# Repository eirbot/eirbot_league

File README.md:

# eirbot_league
Rocket League inspired robots

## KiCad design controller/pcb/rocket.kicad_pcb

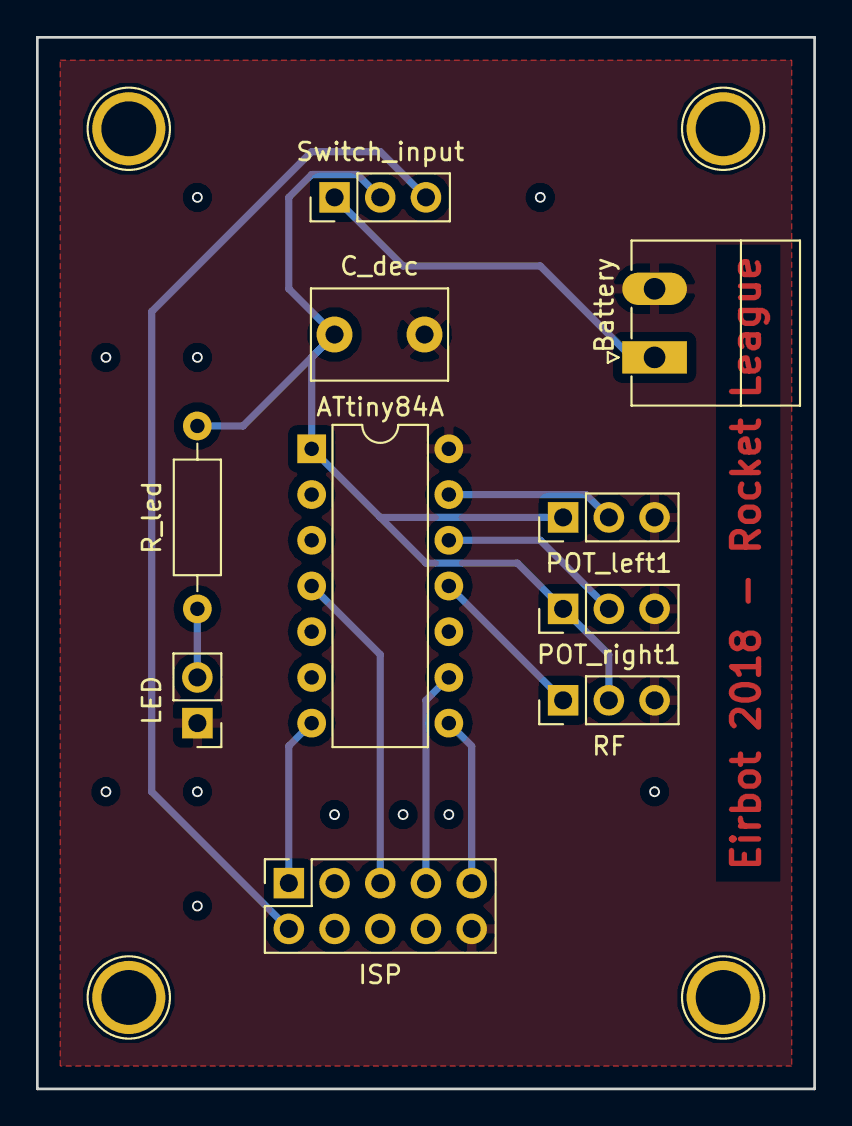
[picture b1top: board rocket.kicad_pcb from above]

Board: 2 copper layers, 43.2 x 58.4 mm, 10 parts (0 on the bottom side), 12 nets.

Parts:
ATtiny84A: ATtiny84A-PU; DIP-14_W7.62mm
Battery: Conn_01x02_Male; PhoenixContact_MC-G_02x3.81mm_Angled
C_dec: 10 nF; C_Disc_D7.5mm_W5.0mm_P5.00mm
ISP: Conn_02x05_Odd_Even; Pin_Header_Straight_2x05_Pitch2.54mm
LED: Conn_01x02_Female; Pin_Header_Straight_1x02_Pitch2.54mm
POT_left1: 10 kR; Pin_Header_Straight_1x03_Pitch2.54mm
POT_right1: 10 kR; Pin_Header_Straight_1x03_Pitch2.54mm
RF: Conn_01x03_Female; Pin_Header_Straight_1x03_Pitch2.54mm
R_led: R_led; R_Axial_DIN0207_L6.3mm_D2.5mm_P10.16mm_Horizontal
Switch_input: Conn_01x03_Female; Pin_Header_Straight_1x03_Pitch2.54mm

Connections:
GND: ATtiny84A.14, Battery.2, C_dec.2, ISP.10, LED.1, POT_left1.3, POT_right1.3, RF.3
unnamed: ATtiny84A.1, C_dec.1, POT_left1.1, POT_right1.1, RF.2, R_led.1, Switch_input.2
unnamed: LED.2, R_led.2
unnamed: Battery.1, Switch_input.1
unnamed: ATtiny84A.7, ISP.1
unnamed: ISP.2, Switch_input.3
unnamed: ATtiny84A.4, ISP.5
unnamed: ATtiny84A.9, ISP.7
unnamed: ATtiny84A.8, ISP.9
unnamed: ATtiny84A.12, POT_right1.2
unnamed: ATtiny84A.13, POT_left1.2
unnamed: ATtiny84A.11, RF.1

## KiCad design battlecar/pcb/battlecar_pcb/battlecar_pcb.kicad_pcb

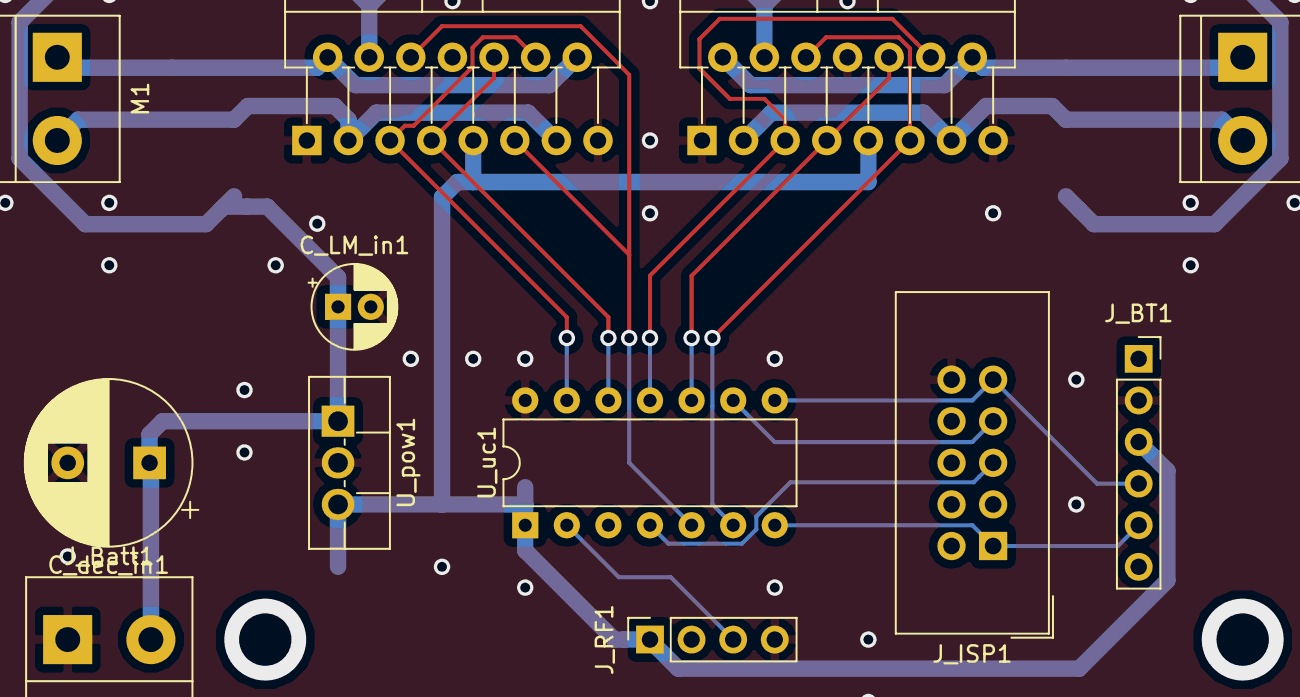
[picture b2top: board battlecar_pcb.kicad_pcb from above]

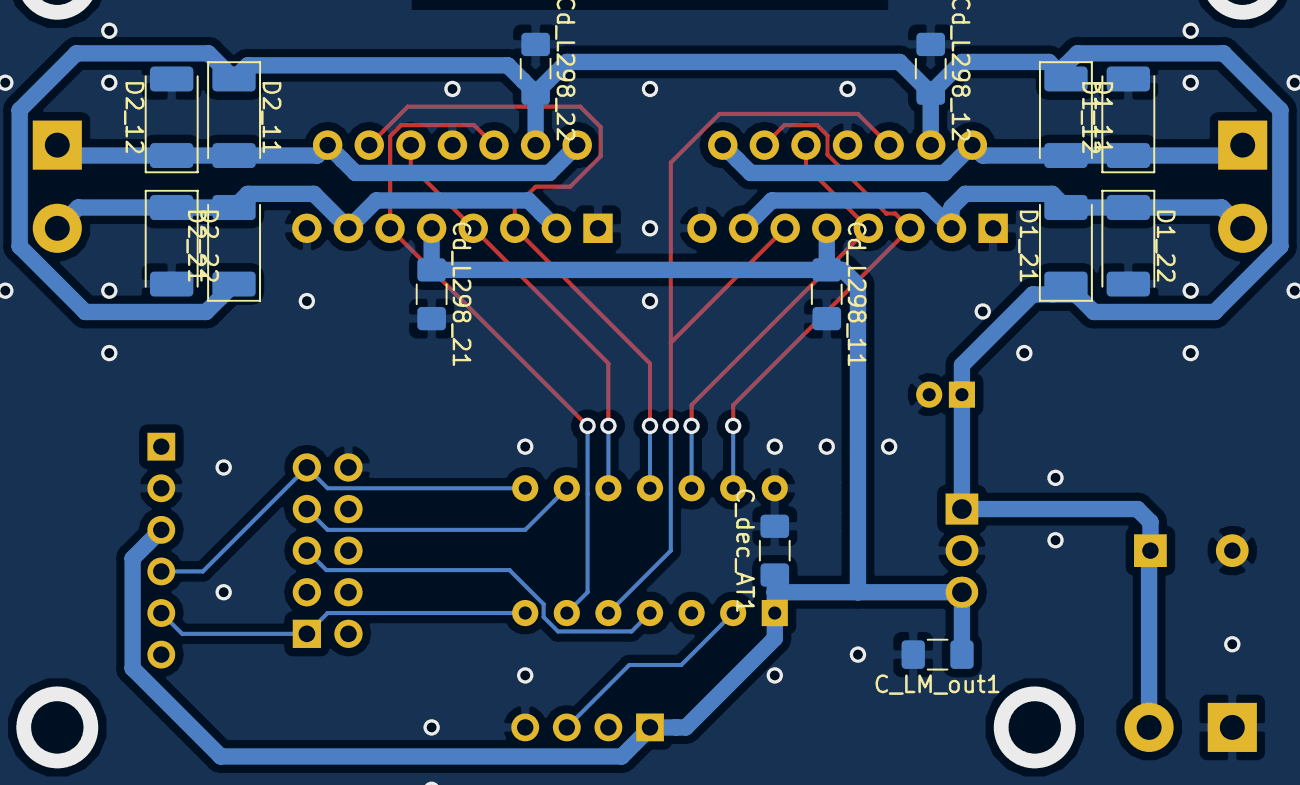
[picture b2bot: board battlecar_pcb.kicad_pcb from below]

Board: 2 copper layers, 26 parts (14 on the bottom side), 18 nets.

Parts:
C_LM_in1: 330nF; CP_Radial_D5.0mm_P2.00mm
C_LM_out1: 0.1uF; C_1206_3216Metric_Pad1.42x1.75mm_HandSolder
C_dec_AT1: 100nF; C_1206_3216Metric_Pad1.42x1.75mm_HandSolder
C_dec_in1: 220uF; CP_Radial_D10.0mm_P5.00mm
Cd_L298_11, Cd_L298_12, Cd_L298_21, Cd_L298_22: 100nF; C_1206_3216Metric_Pad1.42x1.75mm_HandSolder
D1_11, D1_12, D1_21, D1_22, D2_11, D2_12, D2_21, D2_22: 1N007; D_2010_5025Metric_Pad1.52x2.65mm_HandSolder
J_BT1: Conn_01x06; PinSocket_1x06_P2.54mm_Vertical
J_Batt1: Conn_01x02; TerminalBlock_bornier-2_P5.08mm
J_ISP1: Conn_02x05_Odd_Even; IDC-Header_2x05_P2.54mm_Vertical
J_RF1: Conn_01x04; PinSocket_1x04_P2.54mm_Vertical
M1, M2: Motor_DC; TerminalBlock_bornier-2_P5.08mm
U_L298_1, U_L298_2: L298HN; TO-220-15_P2.54x2.54mm_StaggerOdd_Lead4.58mm_Vertical
U_pow1: L7805; TO-220F-3_Vertical
U_uc1: ATtiny84A-PU; DIP-14_W7.62mm

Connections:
+5V: C_LM_out1.1, C_dec_AT1.1, Cd_L298_11.1, Cd_L298_21.1, J_BT1.3, J_RF1.1, U_L298_1.9, U_L298_2.9, U_pow1.3, U_uc1.1
GND: C_LM_in1.2, C_LM_out1.2, C_dec_AT1.2, C_dec_in1.2, Cd_L298_11.2, Cd_L298_12.1, Cd_L298_21.2, Cd_L298_22.1, D1_12.2, D1_22.2, D2_12.2, D2_22.2, J_BT1.2, J_Batt1.1, J_ISP1.10, J_RF1.4, U_L298_1.1, U_L298_1.8, U_L298_1.15, U_L298_2.1, U_L298_2.8, U_L298_2.15, U_pow1.2, U_uc1.14
unnamed: D1_11.2, D1_12.1, M1.1, U_L298_1.2, U_L298_1.14
unnamed: D1_21.2, D1_22.1, M1.2, U_L298_1.3, U_L298_1.13
unnamed: D2_11.2, D2_12.1, M2.1, U_L298_2.2, U_L298_2.14
unnamed: D2_21.2, D2_22.1, M2.2, U_L298_2.3, U_L298_2.13
unnamed: J_BT1.4, J_ISP1.9, U_uc1.8
unnamed: J_BT1.5, J_ISP1.1, U_uc1.7
unnamed: J_ISP1.5, U_uc1.4
unnamed: J_ISP1.7, U_uc1.9
unnamed: J_RF1.3, U_uc1.2
unnamed: U_L298_1.7, U_L298_1.10, U_uc1.12
unnamed: U_L298_1.6, U_L298_1.11, U_uc1.5
unnamed: U_L298_1.5, U_L298_1.12, U_uc1.13
unnamed: U_L298_2.7, U_L298_2.10, U_uc1.10
unnamed: U_L298_2.6, U_L298_2.11, U_uc1.6
unnamed: U_L298_2.5, U_L298_2.12, U_uc1.11
VDC: C_LM_in1.1, C_dec_in1.1, Cd_L298_12.2, Cd_L298_22.2, D1_11.1, D1_21.1, D2_11.1, D2_21.1, J_Batt1.2, U_L298_1.4, U_L298_2.4, U_pow1.1

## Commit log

2019-01-15 Add motor driver schematic and netlist
2019-01-17 Add PCB and update netlist
2019-01-17 Add export files
2019-01-22 Complete pcb
2019-01-22 Update exports
2019-01-22 Add old controller
2019-09-10 Add source files
